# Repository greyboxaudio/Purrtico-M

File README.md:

# Purrtico-M
 
Based on the AMEK MZ-15-RN Equalizer

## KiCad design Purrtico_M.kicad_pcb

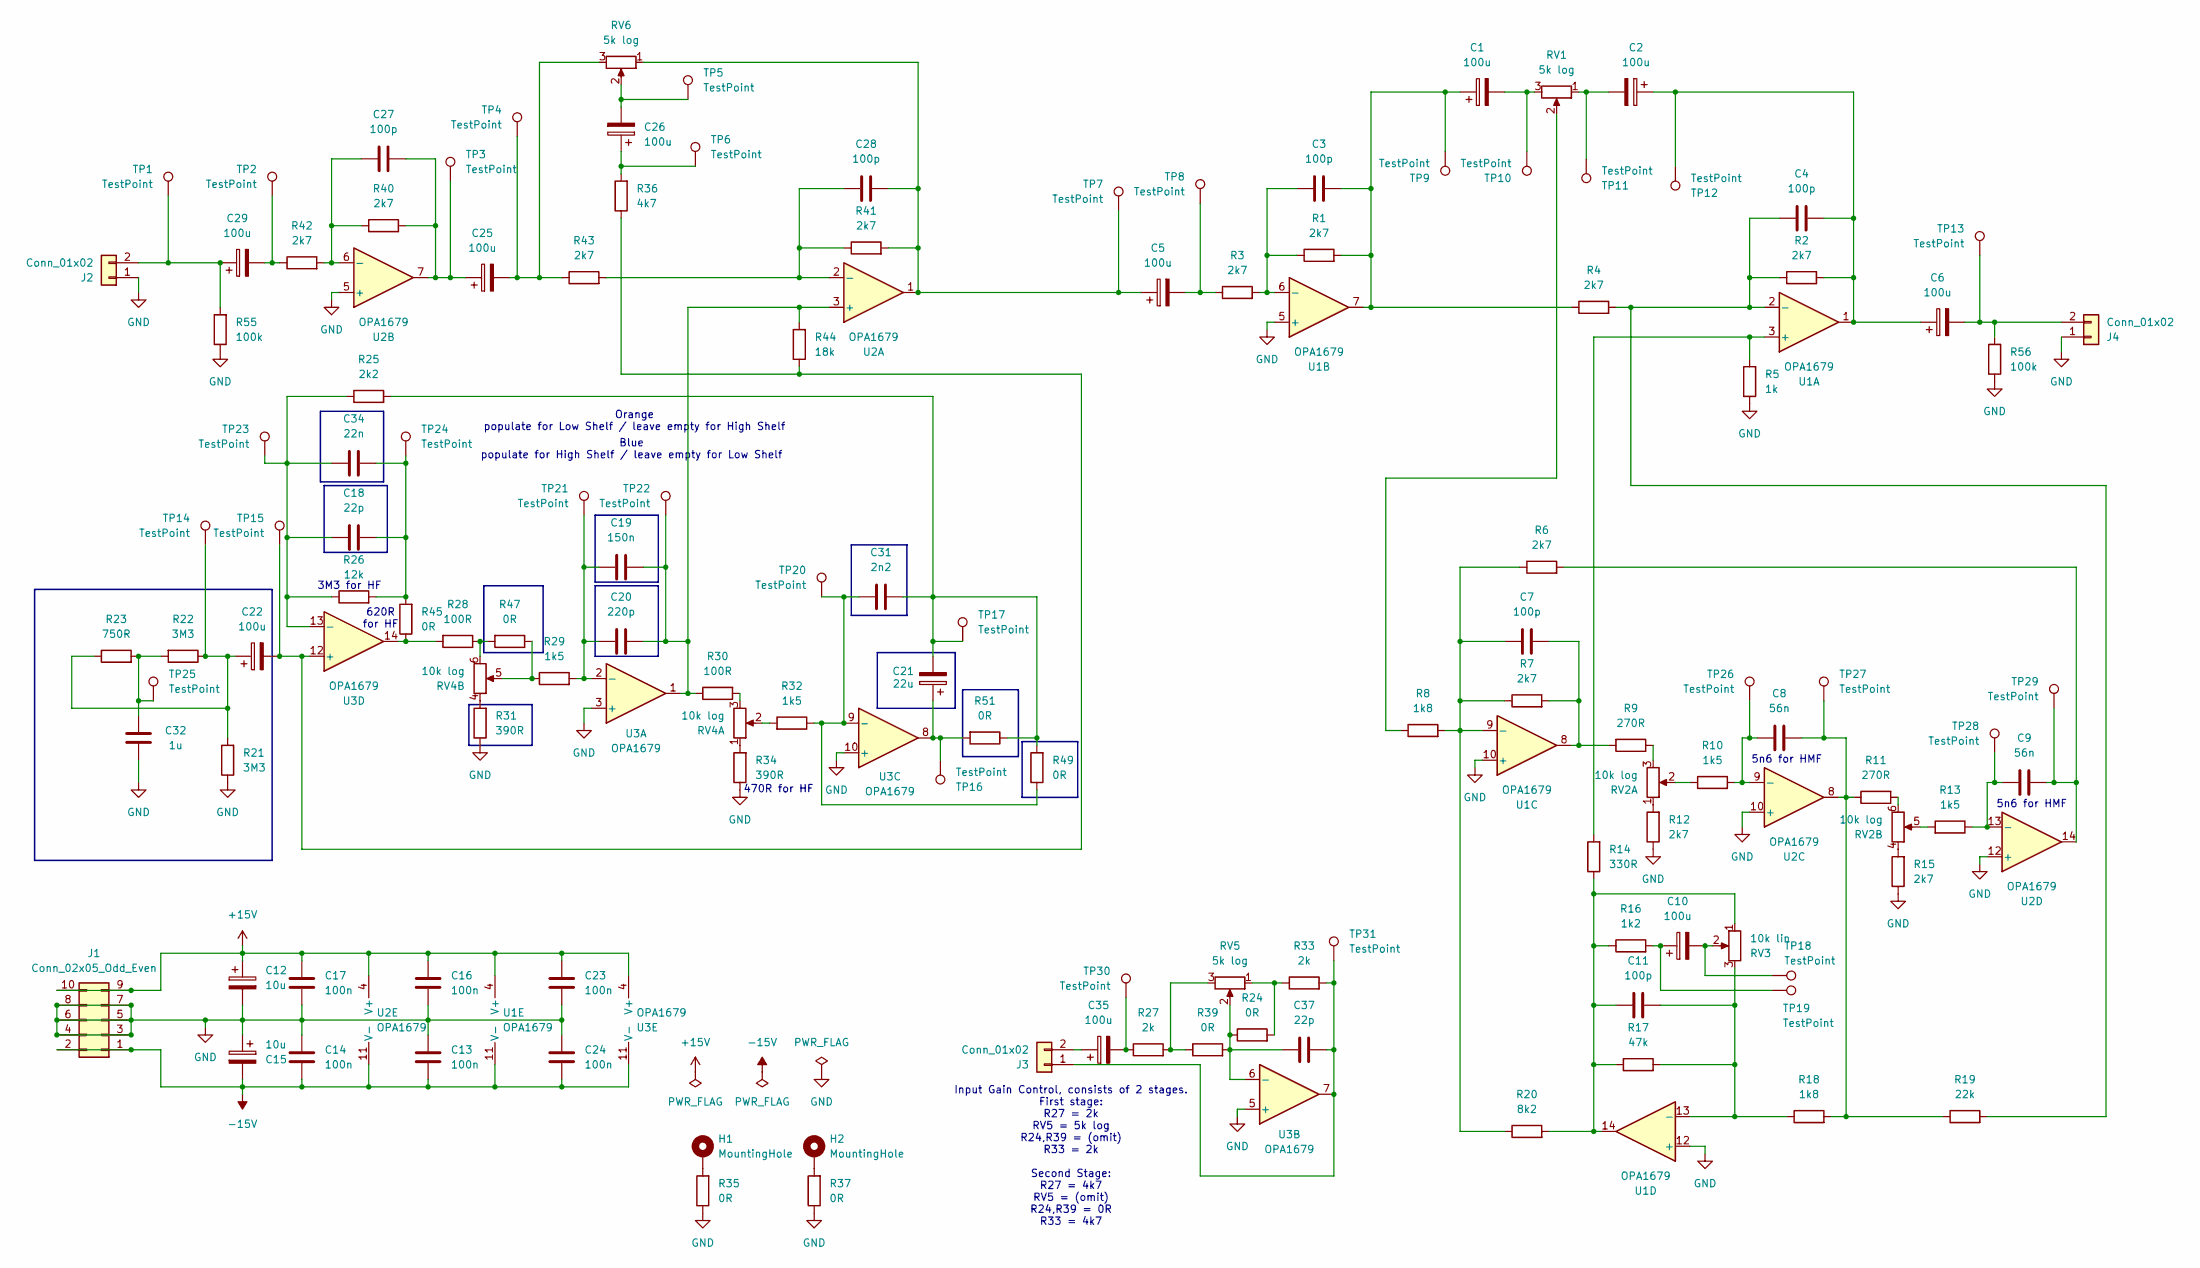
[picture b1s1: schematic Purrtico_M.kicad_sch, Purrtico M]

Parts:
C1, C2, C5, C6, C10, C22, C25, C26, C29, C35: 100u; CP_Radial_D6.3mm_P2.50mm
C3, C4, C7, C11, C27, C28: 100p; C_1206_3216Metric
C8, C9: 56n; C_Rect_L7.2mm_W2.5mm_P5.00mm_FKS2_FKP2_MKS2_MKP2
C12, C15: 10u; CP_Radial_D6.3mm_P2.50mm
C13, C14, C16, C17, C23, C24: 100n; C_1206_3216Metric
C18, C37: 22p; C_1206_3216Metric
C19: 150n; C_Rect_L7.2mm_W2.5mm_P5.00mm_FKS2_FKP2_MKS2_MKP2
C20: 220p; C_1206_3216Metric
C21: 22u; CP_Radial_D6.3mm_P2.50mm
C31: 2n2; C_Rect_L7.2mm_W2.5mm_P5.00mm_FKS2_FKP2_MKS2_MKP2
C32: 1u; C_Rect_L7.2mm_W2.5mm_P5.00mm_FKS2_FKP2_MKS2_MKP2
C34: 22n; C_Rect_L7.2mm_W2.5mm_P5.00mm_FKS2_FKP2_MKS2_MKP2
H1, H2: MountingHole; MountingHole_3.2mm_M3_DIN965_Pad
J1: Conn_02x05_Odd_Even; PinHeader_2x05_P2.54mm_Vertical
J2, J3, J4: Conn_01x02; PinHeader_1x02_P2.54mm_Vertical
R1, R2, R3, R4, R6, R7, R12, R15, R40, R41, R42, R43: 2k7; R_1206_3216Metric
R5: 1k; R_1206_3216Metric
R8, R18: 1k8; R_1206_3216Metric
R9, R11: 270R; R_1206_3216Metric
R10, R13, R29, R32: 1k5; R_1206_3216Metric
R14: 330R; R_1206_3216Metric
R16: 1k2; R_1206_3216Metric
R17: 47k; R_1206_3216Metric
R19: 22k; R_1206_3216Metric
R20: 8k2; R_1206_3216Metric
R21, R22: 3M3; R_1206_3216Metric
R23: 750R; R_1206_3216Metric
R24, R35, R37, R39, R45, R47, R49, R51: 0R; R_1206_3216Metric
R25: 2k2; R_1206_3216Metric
R26: 12k; R_1206_3216Metric
R27, R33: 2k; R_1206_3216Metric
R28, R30: 100R; R_1206_3216Metric
R31, R34: 390R; R_1206_3216Metric
R36: 4k7; R_1206_3216Metric
R44: 18k; R_1206_3216Metric
R55, R56: 100k; R_1206_3216Metric
RV1, RV5, RV6: 5k log; PinHeader_1x03_P2.54mm_Vertical
RV2, RV4: 10k log; PinHeader_2x03_P2.54mm_Vertical
RV3: 10k lin; PinHeader_1x03_P2.54mm_Vertical
TP1, TP2, TP3, TP4, TP5, TP6, TP7, TP8, TP9, TP10, TP11, TP12, TP13, TP14, TP15, TP16, TP17, TP18, TP19, TP20, TP21, TP22, TP23, TP24, TP25, TP26, TP27, TP28, TP29, TP30, TP31: TestPoint; TestPoint_THTPad_D1.0mm_Drill0.5mm
U1, U2, U3: OPA1679; SOIC-14_3.9x8.7mm_P1.27mm

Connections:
+15V: C12.1, C16.2, C17.2, C23.2, J1.9, J1.10, U1.4 (V+), U2.4 (V+), U3.4 (V+)
-15V: C13.1, C14.1, C15.2, C24.1, J1.1, J1.2, U1.11 (V-), U2.11 (V-), U3.11 (V-)
GND: C12.2, C13.2, C14.2, C15.1, C16.1, C17.1, C23.1, C24.2, C32.2, J1.3, J1.4, J1.5, J1.6, J1.7, J1.8, J2.1, J4.1, R5.1, R12.1, R15.1, R21.1, R31.1, R34.1, R35.1, R37.1, R55.1, R56.1, U1.5 (+), U1.10 (+), U1.12 (+), U2.5 (+), U2.10 (+), U2.12 (+), U3.3 (+), U3.5 (+), U3.10 (+)
unnamed: C1.1, C3.2, R1.2, R4.1, TP9.1, U1.7
unnamed: C1.2, RV1.3, TP10.1
unnamed: C2.1, C4.2, C6.1, R2.2, TP12.1, U1.1
unnamed: C2.2, RV1.1, TP11.1
unnamed: C5.2, R3.1, TP8.1
unnamed: C7.2, R7.2, R9.2, U1.8
unnamed: C8.2, R11.1, R18.2, R19.1, TP27.1, U2.8
unnamed: C9.2, R6.2, TP29.1, U2.14
unnamed: C10.1, R16.2, TP19.1
unnamed: C10.2, RV3.2, TP18.1
unnamed: C11.1, R14.1, R16.1, R17.1, R20.2, RV3.1, U1.14
unnamed: C18.2, C34.2, R26.2, R45.2, TP24.1
unnamed: C21.1, R51.2, TP16.1, U3.8
unnamed: C21.2, C31.2, R25.2, R49.2, R51.1, TP17.1
unnamed: C22.1, R21.2, R22.1, R23.1, TP14.1
unnamed: C25.1, C27.2, R40.2, TP3.1, U2.7
unnamed: C25.2, R43.1, RV6.3, TP4.1
unnamed: C26.1, R36.2, TP6.1
unnamed: C26.2, RV6.2, TP5.1
unnamed: C5.1, C28.2, R41.2, RV6.1, TP7.1, U2.1
unnamed: C29.2, R42.1, TP2.1
unnamed: C32.1, R22.2, R23.2, TP25.1
unnamed: C35.2, R27.1, TP30.1
unnamed: H1.1, R35.2
unnamed: H2.1, R37.2
unnamed: C29.1, J2.2, R55.2, TP1.1
unnamed: C37.1, J3.1, R33.2, TP31.1, U3.7
unnamed: C35.1, J3.2
unnamed: C6.2, J4.2, R56.2, TP13.1
unnamed: R8.1, RV1.2
unnamed: R9.1, RV2.3
unnamed: R10.1, RV2.2
unnamed: R11.2, RV2.6
unnamed: R12.2, RV2.1
unnamed: R13.2, RV2.5
unnamed: R15.2, RV2.4
unnamed: R24.2, R33.1, RV5.1
unnamed: R27.2, R39.1, RV5.3
unnamed: R28.1, R47.2, RV4.6
unnamed: R28.2, R45.1, U3.14
unnamed: R29.1, R47.1, RV4.5
unnamed: R30.2, RV4.3
unnamed: R31.2, RV4.4
unnamed: R32.2, RV4.2
unnamed: R34.2, RV4.1
unnamed: R5.2, R14.2, U1.3 (+)
unnamed: C4.1, R2.1, R4.2, R19.2, U1.2 (-)
unnamed: C3.1, R1.1, R3.2, U1.6 (-)
unnamed: C7.1, R6.1, R7.1, R8.2, R20.1, U1.9 (-)
unnamed: C11.2, R17.2, R18.1, RV3.3, U1.13 (-)
unnamed: C19.2, C20.2, R30.1, R44.2, TP22.1, U2.3 (+), U3.1
unnamed: C28.1, R41.1, R43.2, U2.2 (-)
unnamed: C27.1, R40.1, R42.2, U2.6 (-)
unnamed: C8.1, R10.2, TP26.1, U2.9 (-)
unnamed: C9.1, R13.1, TP28.1, U2.13 (-)
unnamed: C19.1, C20.1, R29.2, TP21.1, U3.2 (-)
unnamed: C37.2, R24.1, R39.2, RV5.2, U3.6 (-)
unnamed: C31.1, R32.1, R49.1, TP20.1, U3.9 (-)
unnamed: C22.2, R36.1, R44.1, TP15.1, U3.12 (+)
unnamed: C18.1, C34.1, R25.1, R26.1, TP23.1, U3.13 (-)

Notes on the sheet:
5n6 for HMF
470R for HF
Input Gain Control, consists of 2 stages. First stage: R27 = 2k RV5 = 5k log R24,R39 = (omit) R33 = 2k Second Stage: R27 = 4k7 RV5 = (omit) R24,R39 = 0R R33 = 4k7
3M3 for HF
620R for HF
Orange populate for Low Shelf / leave empty for High Shelf
Blue populate for High Shelf / leave empty for Low Shelf

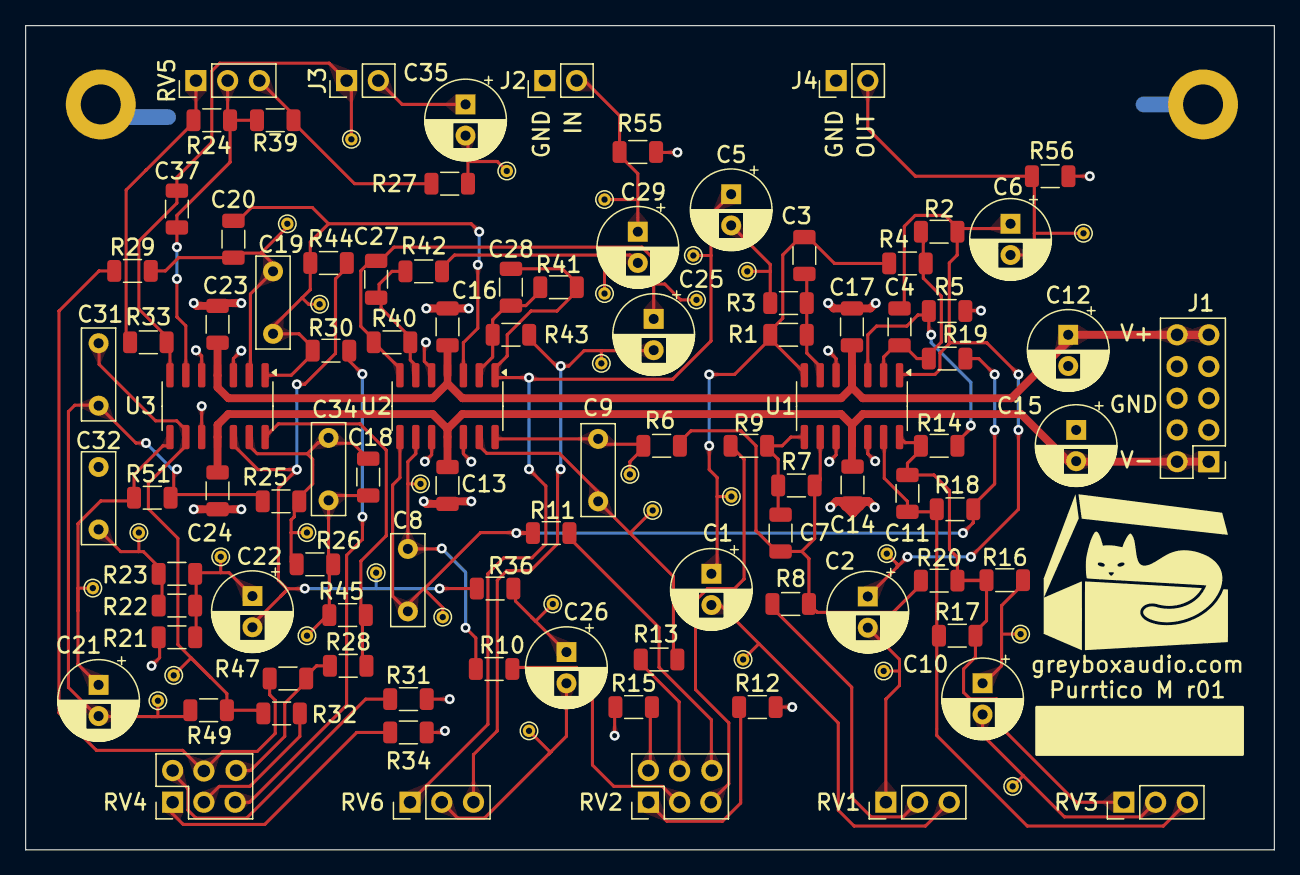
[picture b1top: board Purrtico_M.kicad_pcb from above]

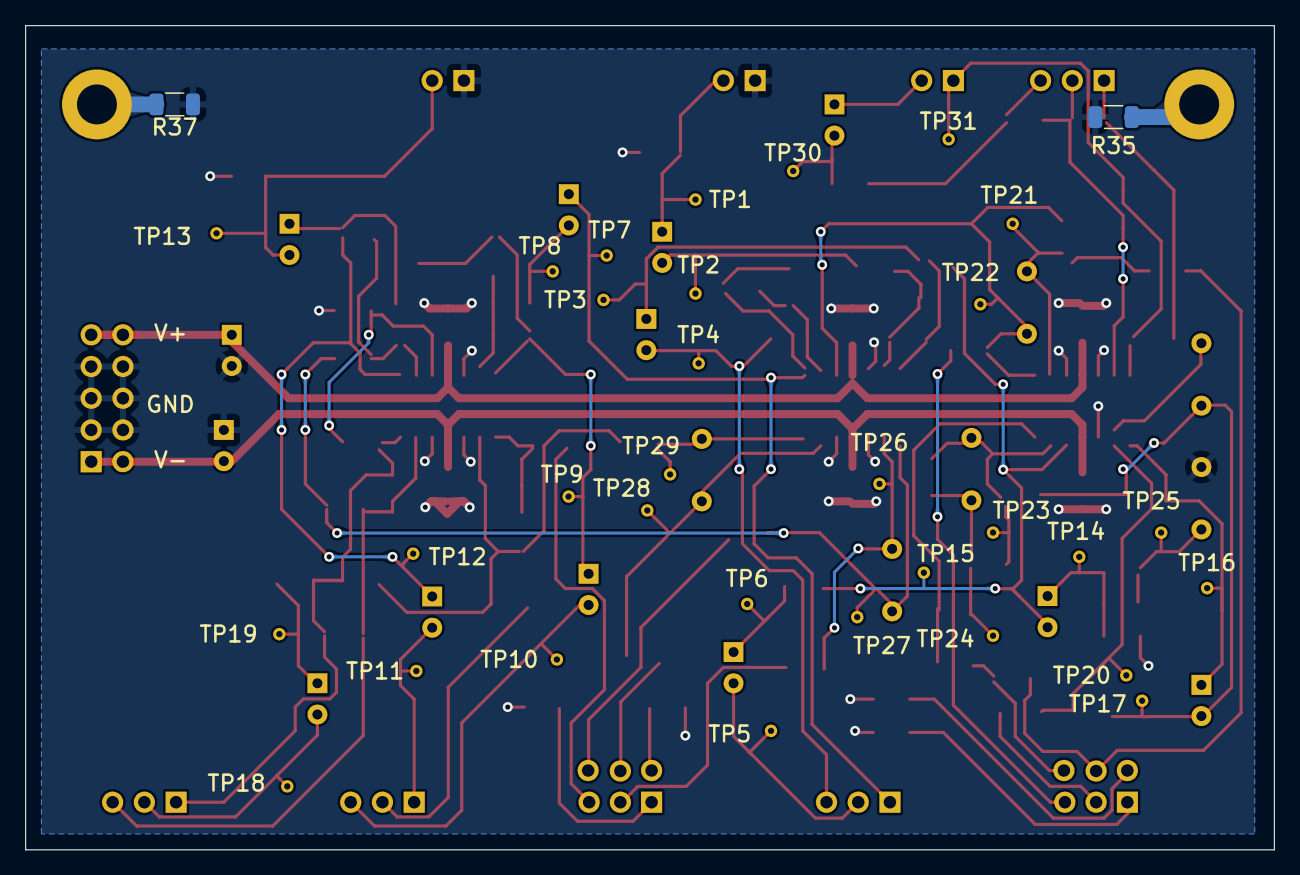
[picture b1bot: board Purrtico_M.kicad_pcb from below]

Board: 2 copper layers, 100.0 x 66.0 mm, 129 parts (2 on the bottom side), 63 nets.

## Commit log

2024-07-18 started pcb
2024-07-18 update pcb
2024-07-19 all connected
2024-07-20 update routing
2024-07-21 added shelving band
2024-07-21 modified shelving filter
2024-07-21 whatever
2024-07-22 everything's routed
2024-07-23 changed pcb size
2024-07-24 refine layout
2024-07-24 added tespoints
2024-07-24 flipped text on backside
2024-07-30 first update after testing
    shelving circuit not working for whatever reason :/
2024-07-30 add pdf
2024-07-31 update schematic
2024-08-01 update pcb
    added 470p cap as MLCC, removed two mounting holes to create space for wider potentiometer spacing, swapped rows of RV6 to enable the use of a single gang potentiometer for the high shelf
2024-08-02 update pcb
    swapped potentiometer pinouts, increased potentiometer spacing on pcb
2024-08-02 clean up pcb
2024-08-03 tweak LF EQ
2024-08-05 tuned low shelf
    tuned the low shelf so that it closely matches the 5033
2024-08-05 update high shelf
2024-08-06 added input gain control
2024-08-14 added 0R for mounting holes
    as well as some small layout refinements
2024-08-15 update potentiometer values
2024-08-16 added gerber files
2025-01-19 updated comments
